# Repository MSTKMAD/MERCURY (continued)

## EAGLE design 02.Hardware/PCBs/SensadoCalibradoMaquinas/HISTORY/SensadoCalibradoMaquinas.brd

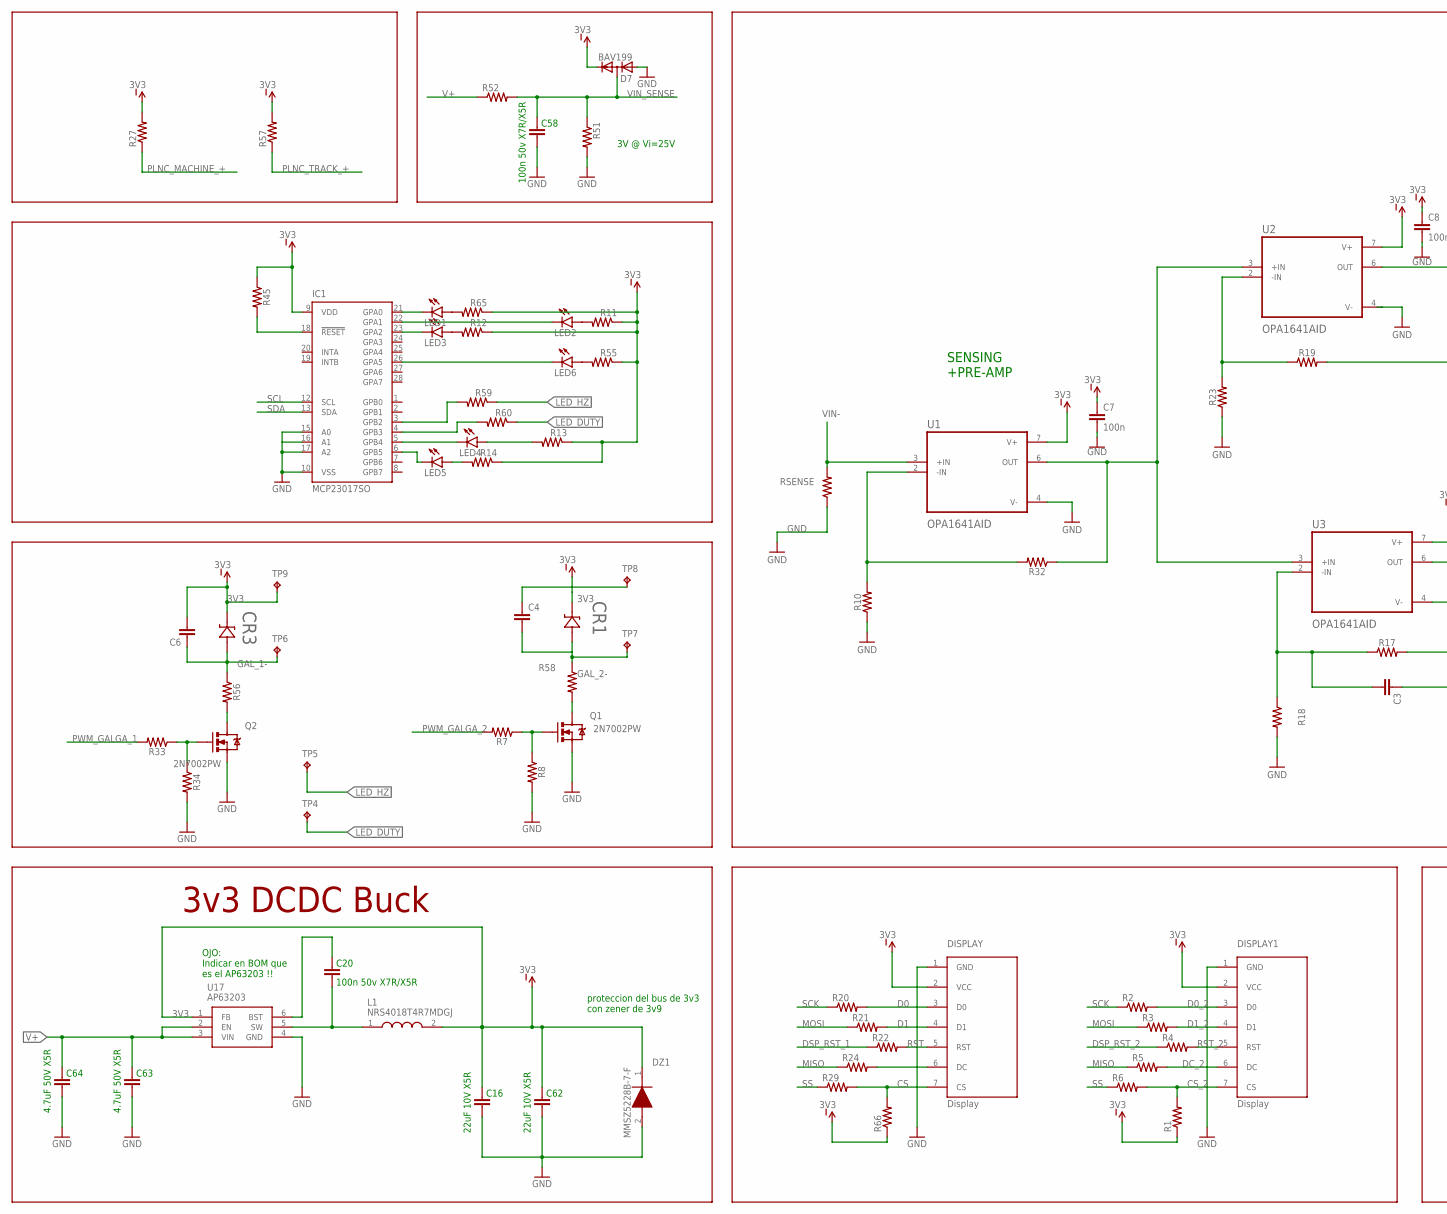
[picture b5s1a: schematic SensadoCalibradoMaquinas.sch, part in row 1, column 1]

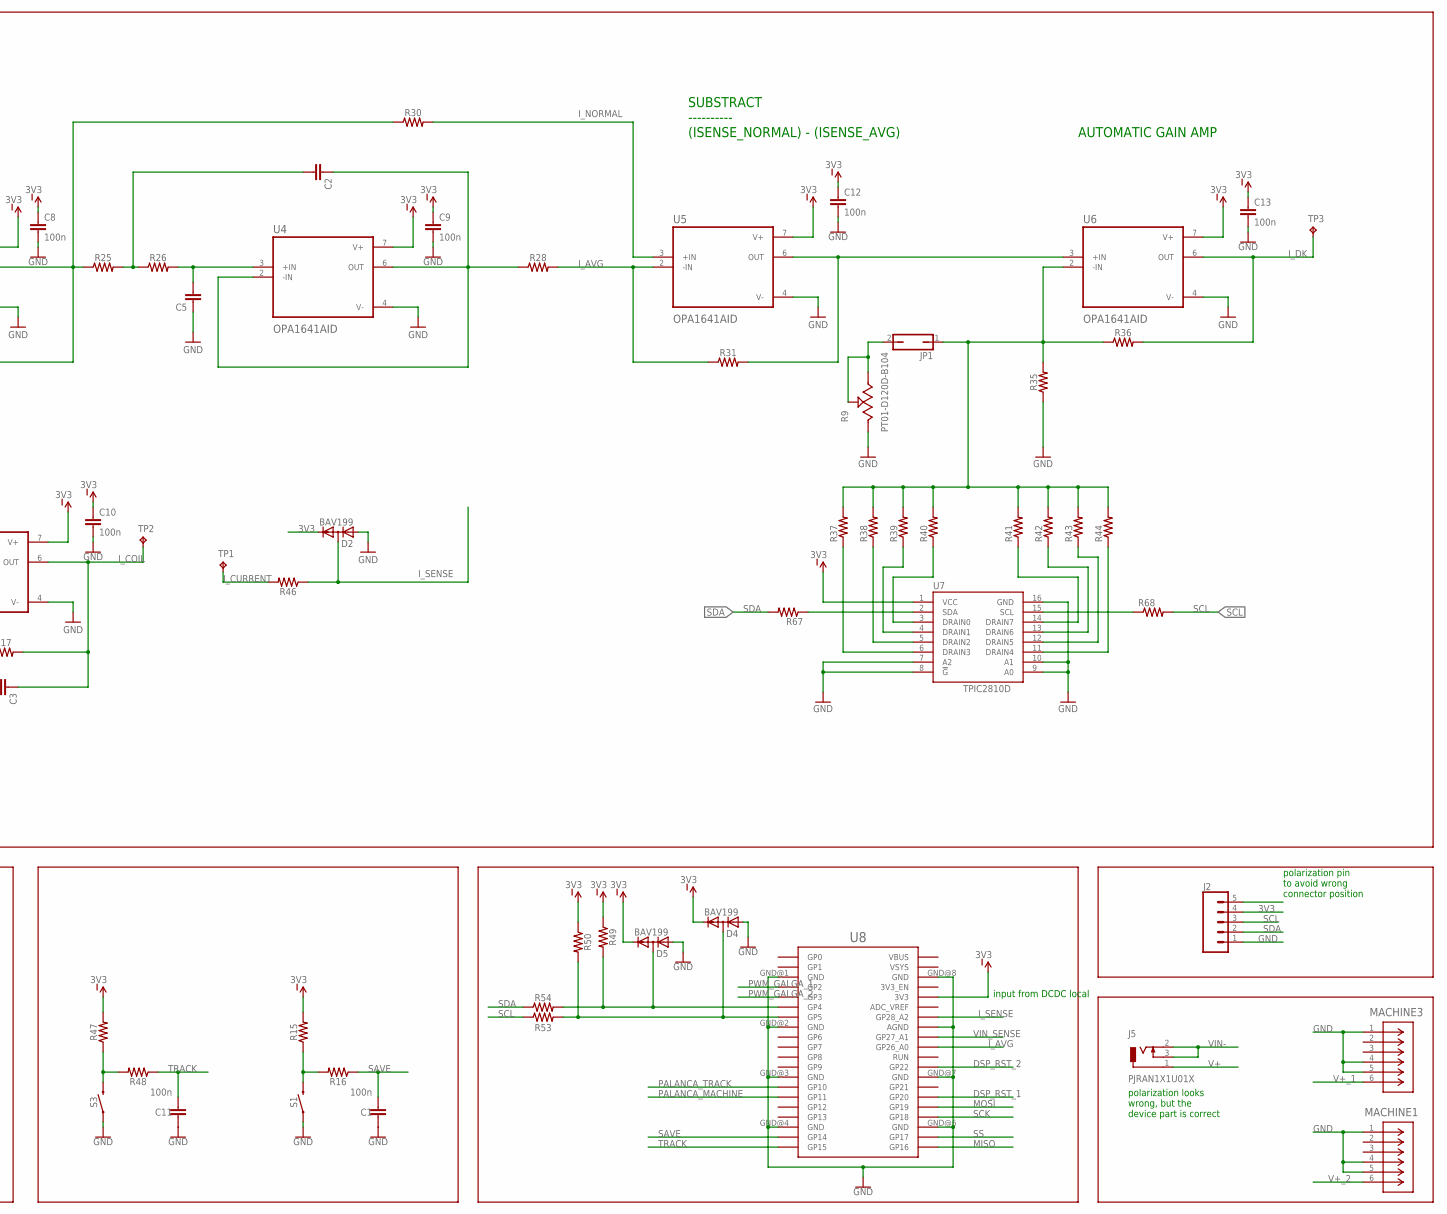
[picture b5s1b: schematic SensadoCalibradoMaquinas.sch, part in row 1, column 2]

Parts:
C1, C7, C8, C9, C10, C11, C12, C13: 100n; 0805
C2, C3, C4, C5, C6: CAP0805; 0805
C16, C62: 22uF 10V X5R; 0805
C20, C58: 100n 50v X7R/X5R; 0805
C63, C64: 4.7uF 50V X5R; 0805
CR1, CR3: STPS1L40U; SMB_STM
D2, D4, D5, D7: BAV199; SOT23
DISPLAY, DISPLAY1: Display; OLED_LCD
DZ1: MMSZ5228B-7-F; SODFL3518X115N
IC1: MCP23017SO; SO28W
J2: CONN_05; 1X05
J5: PJRAN1X1U01X
JP1: JP1Q; JP1
L1: NRS4018T4R7MDGJ; NRS4018T100MDGJ
LED1, LED2, LED3, LED4, LED5, LED6: LED3MM
MACHINE1, MACHINE3: ACJS-MHDR; CONN_MHDR_AMP
Q1, Q2: 2N7002PW; SOT323
R1, R2, R3, R4, R5, R6, R7, R8, R10, R11, R12, R13, R14, R15, R16, R17, R18, R19, R20, R21, R22, R23, R24, R25, R26, R27, R28, R29, R30, R31, R32, R33, R34, R35, R36, R37, R38, R39, R40, R41, R42, R43, R44, R45, R46, R47, R48, R49, R50, R51, R52, R53, R54, R55, R56, R57, R58, R59, R60, R65, R66, R67, R68: 0805
R9: PT01-D120D-B104; TRIM_PT01-D120D-B104
RSENSE: AXIAL-0.3
S1, S3: MOMENTARY-SWITCH-SPST-SMD-5.2MM; TACTILE_SWITCH_SMD_5.2MM
TP1, TP2, TP3, TP4, TP5, TP6, TP7, TP8, TP9: TPTP06SQ; TP06SQ
U1, U2, U3, U4, U5, U6: OPA1641AID; SOIC127P599X175-8N
U7: TPIC2810D; SO16
U8: RPI_PICO_IG-TH; RPI_PICO_TH
U17: AP63203; SOT95P280X100-6N

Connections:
3V3: C4.1, C6.2, C7.2, C8.2, C9.2, C10.2, C12.2, C13.2, C16.2, C62.2, CR1.2, CR3.2, D2.2 (C), D4.2 (C), D5.2 (C), D7.2 (C), DISPLAY.2 (VCC), DISPLAY1.2 (VCC), DZ1.1 (K), IC1.9 (VDD), J2.4, L1.2, R1.1, R11.1, R12.1, R13.1, R14.1, R15.2, R27.2, R45.1, R47.2, R49.1, R50.1, R55.1, R57.2, R65.1, R66.1, TP8.TP, TP9.TP, U1.7 (V+), U2.7 (V+), U3.7 (V+), U4.7 (V+), U5.7 (V+), U6.7 (V+), U7.1 (VCC), U8.3V3, U17.1 (FB)
CS: DISPLAY.7 (CS), R29.2, R66.2
CS_2: DISPLAY1.7 (CS), R1.2, R6.2
D0: DISPLAY.3 (D0), R20.2
D0_2: DISPLAY1.3 (D0), R2.2
D1: DISPLAY.4 (D1), R21.2
D1_2: DISPLAY1.4 (D1), R3.2
DC_2: DISPLAY1.6 (DC), R5.2
DSP_RST_1: R22.1, U8.GP20
DSP_RST_2: R4.1, U8.GP22
GAIN: R32.1, U1.6 (OUT), U2.3 (+IN), U3.3 (+IN)
GAL_1-: C6.1, CR3.1, R56.1, TP6.TP
GAL_2-: C4.2, CR1.1, R58.1, TP7.TP
GND: C1.1, C5.1, C7.1, C8.1, C9.1, C10.1, C11.1, C12.1, C13.1, C16.1, C58.1, C62.1, C63.1, C64.1, D2.1 (A), D4.1 (A), D5.1 (A), D7.1 (A), DISPLAY.1 (GND), DISPLAY1.1 (GND), DZ1.2 (A), IC1.10 (VSS), IC1.15 (A0), IC1.16 (A1), IC1.17 (A2), J2.1, MACHINE1.1, MACHINE1.4, MACHINE1.5, MACHINE3.1, MACHINE3.4, MACHINE3.5, Q1.2 (S), Q2.2 (S), R8.2, R9.1, R10.1, R18.2, R23.1, R34.2, R35.1, R51.2, RSENSE.P$1 (1), S1.1, S3.1, U1.4 (V-), U2.4 (V-), U3.4 (V-), U4.4 (V-), U5.4 (V-), U6.4 (V-), U7.7 (A2), U7.8 (!G), U7.9 (A0), U7.10 (A1), U7.16 (GND), U8.AGND, U8.GND@1 (GND), U8.GND@2 (GND), U8.GND@3 (GND), U8.GND@4 (GND), U8.GND@6 (GND), U8.GND@7 (GND), U8.GND@8 (GND), U17.4 (GND)
I_AVG: R28.2, R31.1, U5.2 (-IN), U8.GP26_A0
I_COIL: C3.1, R17.2, TP2.TP, U3.6 (OUT)
I_CURRENT: R46.2, TP1.TP
I_DK: R36.2, TP3.TP, U6.6 (OUT)
I_NORMAL: R30.2, U5.3 (+IN)
I_SENSE: D2.3 (AC), R46.1, U8.GP28_A2
LED_DUTY: R60.1, TP4.TP
LED_HZ: R59.1, TP5.TP
MISO: R5.1, R24.1, U8.GP16
MOSI: R3.1, R21.1, U8.GP19
unnamed: D5.3 (AC), R49.2, R54.2, U8.GP4
unnamed: Q2.1 (G), R33.1, R34.1
unnamed: Q1.1 (G), R7.1, R8.1
unnamed: R10.2, R32.2, U1.2 (-IN)
unnamed: R31.2, U5.6 (OUT), U6.3 (+IN)
unnamed: LED1.A, R65.2
unnamed: DISPLAY.6 (DC), R24.2
unnamed: IC1.22 (GPA1), LED2.K (C)
unnamed: LED2.A, R11.2
unnamed: IC1.23 (GPA2), LED3.K (C)
unnamed: LED4.A, R13.2
unnamed: IC1.5 (GPB4), LED4.K (C)
unnamed: LED5.A, R14.2
unnamed: IC1.6 (GPB5), LED5.K (C)
unnamed: R15.1, R16.2, S1.3 (2)
unnamed: JP1.1, R35.2, R36.1, R37.2, R38.2, R39.2, R40.2, R41.2, R42.2, R43.2, R44.2, U6.2 (-IN)
unnamed: R37.1, U7.6 (DRAIN3)
unnamed: R38.1, U7.5 (DRAIN2)
unnamed: R39.1, U7.4 (DRAIN1)
unnamed: R40.1, U7.3 (DRAIN0)
unnamed: R41.1, U7.14 (DRAIN7)
unnamed: R42.1, U7.13 (DRAIN6)
unnamed: R43.1, U7.12 (DRAIN5)
unnamed: R44.1, U7.11 (DRAIN4)
unnamed: IC1.3 (GPB2), R59.2
unnamed: R68.1, U7.15 (SCL)
unnamed: IC1.4 (GPB3), R60.2
unnamed: LED6.A, R55.2
unnamed: C2.1, R28.1, U4.2 (-IN), U4.6 (OUT)
unnamed: C2.2, R25.2, R26.1
unnamed: C5.2, R26.2, U4.3 (+IN)
unnamed: R19.2, R25.1, R30.1, U2.6 (OUT)
unnamed: R19.1, R23.2, U2.2 (-IN)
unnamed: C3.2, R17.1, R18.1, U3.2 (-IN)
unnamed: D4.3 (AC), R50.2, R53.2, U8.GP5
unnamed: IC1.26 (GPA5), LED6.K (C)
unnamed: R47.1, R48.2, S3.3 (2)
unnamed: R67.1, U7.2 (SDA)
unnamed: Q2.3 (D), R56.2
unnamed: LED3.A, R12.2
unnamed: Q1.3 (D), R58.2
unnamed: IC1.18 (!RESET), R45.2
unnamed: JP1.2, R9.2, R9.3
unnamed: IC1.21 (GPA0), LED1.K (C)
unnamed: C20.2, U17.6 (BST)
unnamed: C20.1, L1.1, U17.5 (SW)
PALANCA_MACHINE: U8.GP11
PALANCA_TRACK: U8.GP10
PLNC_MACHINE_+: R27.1
PLNC_TRACK_+: R57.1
PWM_GALGA_1: R33.2, U8.GP2
PWM_GALGA_2: R7.2, U8.GP3
RST: DISPLAY.5 (RST), R22.2
RST_2: DISPLAY1.5 (RST), R4.2
SAVE: C1.2, R16.1, U8.GP14
SCK: R2.1, R20.1, U8.GP18
SCL: IC1.12 (SCL), J2.3, R53.1, R68.2
SDA: IC1.13 (SDA), J2.2, R54.1, R67.2
SS: R6.1, R29.1, U8.GP17
TRACK: C11.2, R48.1, U8.GP15
V+: C63.2, C64.2, J5.1, R52.1, U17.2 (EN), U17.3 (VIN)
V+_1: MACHINE3.6
V+_2: MACHINE1.6
VIN-: J5.2, J5.3, RSENSE.P$2 (2), U1.3 (+IN)
VIN_SENSE: C58.2, D7.3 (AC), R51.1, R52.2, U8.GP27_A1

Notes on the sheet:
3v3 DCDC Buck
OJO: Indicar en BOM que es el AP63203 !!
proteccion del bus de 3v3 con zener de 3v9
3V @ Vi=25V
input from DCDC local
polarization pin to avoid wrong connector position
polarization looks wrong, but the device part is correct
SENSING +PRE-AMP
SUBSTRACT ---------- (ISENSE_NORMAL) - (ISENSE_AVG)
AUTOMATIC GAIN AMP

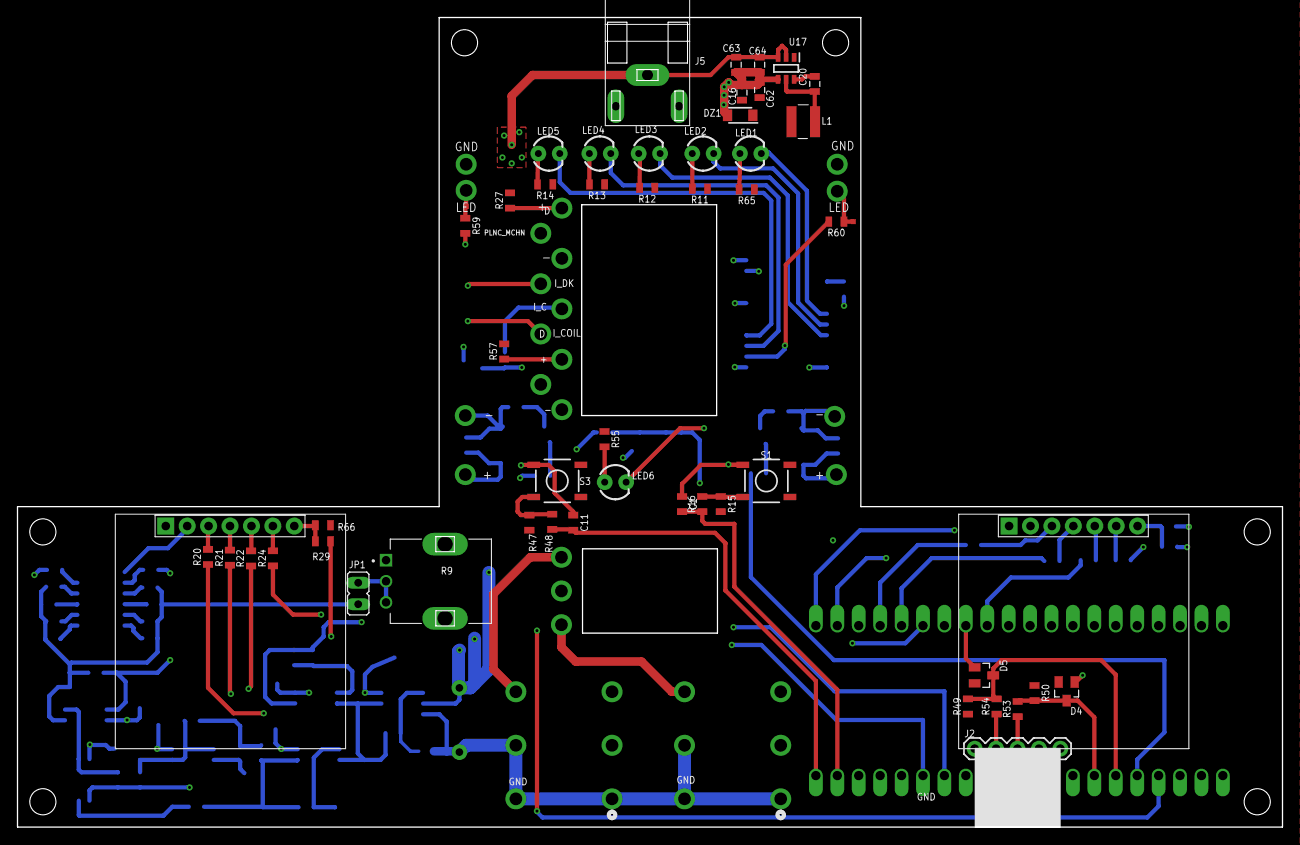
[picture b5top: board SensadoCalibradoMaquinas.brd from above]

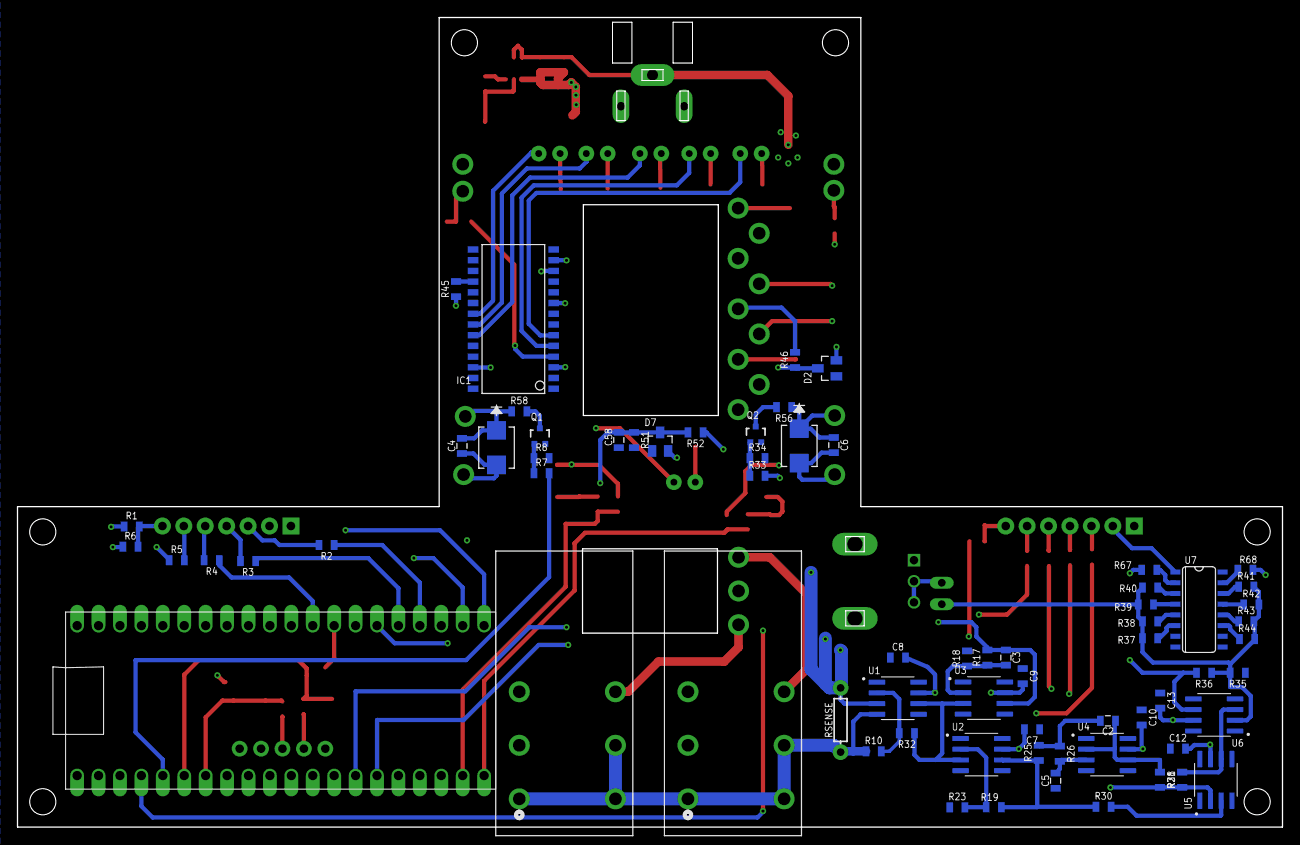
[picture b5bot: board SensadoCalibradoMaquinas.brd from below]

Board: 4 copper layers, 150.0 x 96.0 mm, 128 parts (70 on the bottom side), 83 nets.

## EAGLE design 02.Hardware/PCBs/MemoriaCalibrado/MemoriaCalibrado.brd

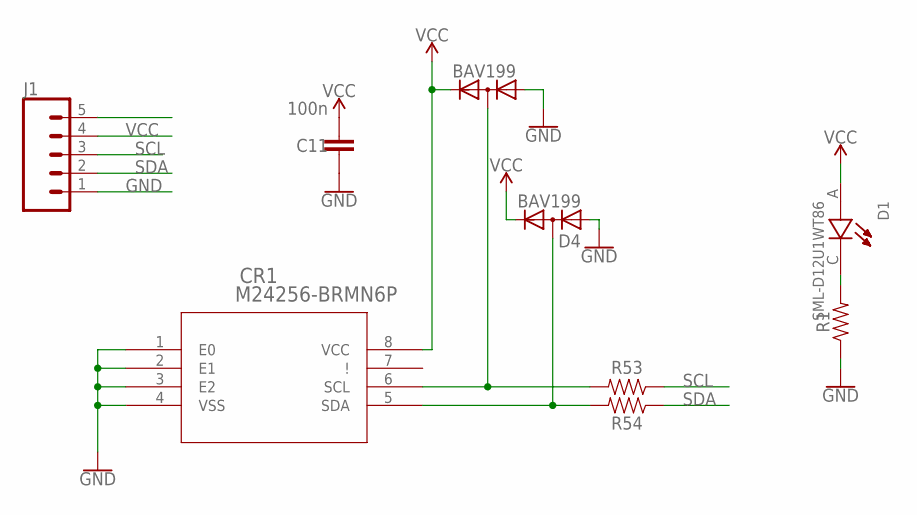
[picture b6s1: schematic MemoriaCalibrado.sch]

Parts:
C11: 100n; 0805
CR1: M24256-BRMN6P; SO-8_STM
D1: SML-D12U1WT86; LED_SML-D12U1WT86
D4, D5: BAV199; SOT23
J1: CONN_05; 1X05
R1, R53, R54: 0805

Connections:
GND: C11.1, CR1.1 (E0), CR1.2 (E1), CR1.3 (E2), CR1.4 (VSS), D4.1 (A), D5.1 (A), J1.1, R1.1
unnamed: CR1.5 (SDA), D4.3 (AC), R54.2
unnamed: D1.C, R1.2
unnamed: CR1.6 (SCL), D5.3 (AC), R53.2
SCL: J1.3, R53.1
SDA: J1.2, R54.1
VCC: C11.2, CR1.8 (VCC), D1.A, D4.2 (C), D5.2 (C), J1.4

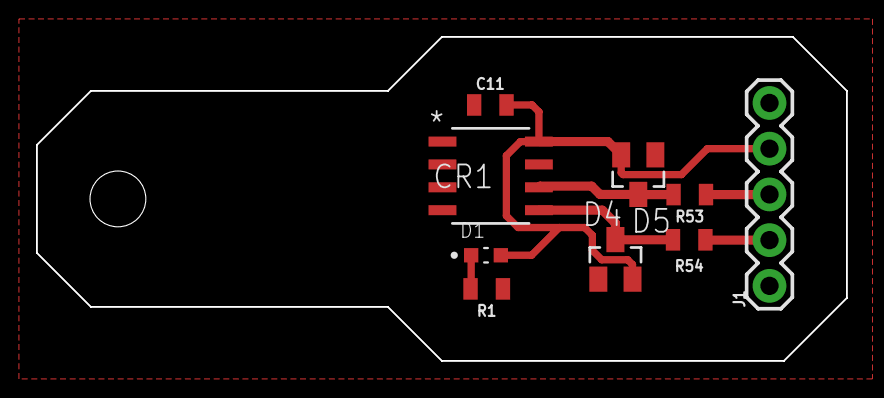
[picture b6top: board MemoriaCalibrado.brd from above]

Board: 2 copper layers, 45.0 x 18.0 mm, 9 parts (0 on the bottom side), 7 nets.

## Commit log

2022-09-05 Creacion PCB Placa de Simulador Sensor Hall
2022-09-08 Creacion PCB v1 Module Motor Driver
2022-09-08 Resistencias en serie en los pulsadores y potenciometro
2022-09-09 Create v1 SimulationSensorHall
    Se añade los binarios adicionalemnte.
2022-09-09 Add RC Antirebotes
2022-09-10 Organizativo
    Eagle files of the Hall simulator to own directory
2022-09-11 Cambios de rutado y nombres
    Cambios de rutado y nombres
2022-09-12 v2 Cambio de conector de entrada y correccion de errores
2022-09-12 v2 Simulador Sensor Hall
    Eliminacion de conector de entrada sensores Hall.
    Reduccion de tamaño.
    Cambio del conector de entrada/salida
    Correccion de errores
2022-09-13 Cambios menores
    Pistas a 0.6 y algunos cambios menores
2022-09-13 GERBER - Enviado a PCBWAY
    Gerber final
2022-09-13 Minor modifications
2022-09-13 CAM GERBER file creado. Enviado a PCBWAY
2022-09-13 Creacion v1 PCB Carrier Motor Driver
2022-09-13 Creacion v1 Interfaz Maxon
2022-09-13 añadido 3v3 a driver de motor
    Para que el AO filtro de ISENSE se alimente a 3v3
    Se actualiza GERBER para PCBWAY
2022-09-13 Se añade 3v3 para filtro ISENSE + Cambios menores
2022-09-14 Se pasa de 4 capas a 2 capas
    El precio del prototipo es casi el doble con 4 caps
2022-09-14 Se genera GERBER para PCBWAY y Cambios menores
2022-09-14 ERC Pasado. Cambios menores
    Al pasar el ERC se detecta fallo en la alimentacion del pull-up de la linea de CS de la pantalla. Se soluciona cambiando a la alimentacion de 3v3.
2022-09-23 Se mueve resistencia de pull-down entrada a pull-down en MOSFET
    Para conseguir crear un tDEAD entre transistores
2022-09-23 Cambios antes de Produccion
2022-09-27 Update Interfaz Motor Maxon.brd
    Planos GND en TOP & BOTTOM
2022-09-27 añadidas vias entre planos masa top y bottom
2022-10-03 Step Motor Control App note
    Se añade una nota de aplicacion del control de los motores paso a paso usando los codigos disponibles en la carpeta correspondiente.
    Se añaden las librerias necesarias.
2022-10-04 Test sensor haptico + Librerias asociada
2022-10-04 Adaptacion del simulador a PCB final.
2022-10-04 Creacion del codigo de control del motor. MotorDriver.ino
    v1 MotorDriver.ino
    Add Librerias nbecesasrias:
    - Adafruit BusIO
    - Adafruit SSD1306
    - AdafruitGFX
    - Millitimer
2022-11-14 Correcion errores. Interfaz Maxon v2
    Correcion de conexiones entre los conectores del motores y los conectores a la placa.
2023-05-10 Adapatacion de la interfaz para conexión por trought hole directamente.
2024-10-30 Tester v1 Motor Faulhaber
2024-10-30 Cambio de Carpeta
2024-10-30 TestBench Antiguo. DEPRECATED. Solo para consulta
2024-10-30 Librerias y Tests
2025-02-10 Adaptacion librerias
2025-02-10 Test Produccion Machine v1
2025-02-10 Test Motor Faulhaber v1
2025-02-10 Eliminacion carpeta StepMotor
2025-02-10 Script para maquina de calibrado
2025-02-10 Sensado de corriente v1
2025-02-10 PCB Motor Faulhaber
2025-02-10 PCB Sensado de corriente maquina
2025-02-10 PCB Motor faulhaber con sensor de temperatura
2025-02-10 PCB sensor hall placa motor para testeo
2025-02-10 PCB de la memoria esterna del calibrado de maquinas
2025-02-10 PCB testeao de los motores faulhaber
2025-02-10 PCB de Resistencias para el testeo del Motor
2025-02-10 PCB Sensado y Calibrado de Maquinas Coil
2025-02-10 PCB Sensor IR pegado al motor.
2025-02-10 Ficheros filtrado de datos para LabView
2025-03-11 Software de teste para emotor Faulhaber
2025-03-11 Rack de pruebas de hasa 18 macquinas v1
2025-03-17 Versiones enviadas a PCB way
2025-03-17 Inclusion de la biblioteca del DAC y salida del dac en velocidad
2025-03-24 New FAllbafe DC CONN
2025-03-24 Version inicial sensor analogico temperatura + CPU attiny85
2025-04-10 fichero cpu en maquina sensado temperatura
2025-04-21 Sensado de voltaje de entrada. version 2
2025-04-22 version020. EEPROM + fix error
    Se sube a la primera linea del digital write.
2025-05-07 v2 Cambio de direccion
2025-05-13 CSVs
2025-05-13 Modificador para invertir el sintio de giro cada poco tiempo.
2025-05-13 Test Vanta Black Endurance v1
2025-07-24 Vanta Black v2
2025-10-08 VantaBlack v4
2025-10-08 Librerias
2025-10-08 PCBs
2026-01-16 Vanta Black Reorder
